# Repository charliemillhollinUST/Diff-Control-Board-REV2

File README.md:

The schematic and PCB were created in KiCad.

Contact <mill70882@stthomas.edu> for access to the software repository.

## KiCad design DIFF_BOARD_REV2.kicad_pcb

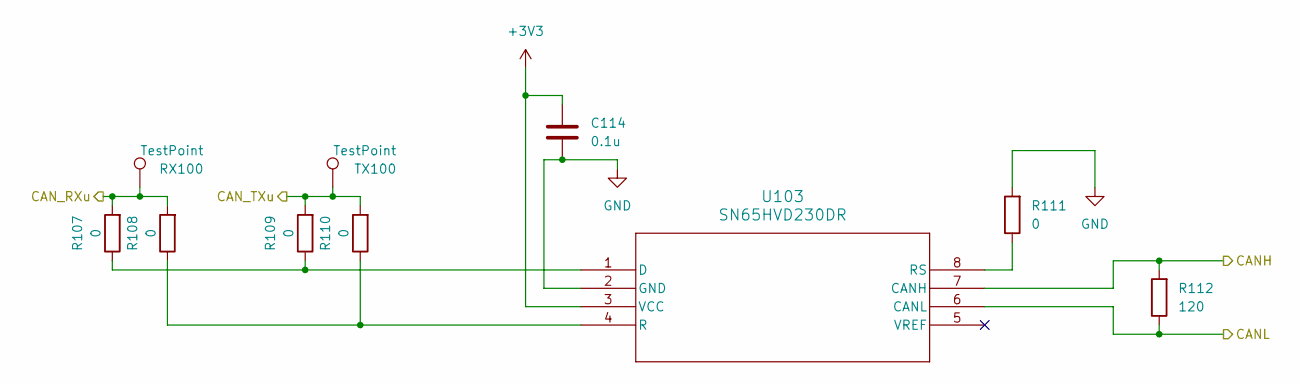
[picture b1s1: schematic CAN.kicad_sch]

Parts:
C114: 0.1u; C_0603_1608Metric_Pad1.08x0.95mm_HandSolder
R107, R108, R109, R110, R111: 0; R_0603_1608Metric_Pad0.98x0.95mm_HandSolder
R112: 120; R_0603_1608Metric_Pad0.98x0.95mm_HandSolder
RX100: TestPoint; TestPoint_Pad_D1.0mm
TX100: TestPoint; TestPoint_Pad_D1.0mm
U103: SN65HVD230DR; D8

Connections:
+3V3: C114.1, U103.3 (VCC); also elsewhere on the board
/CAN/CANH: R112.2, U103.7 (CANH); also elsewhere on the board
/CAN/CANL: R112.1, U103.6 (CANL); also elsewhere on the board
/CAN/CAN_RXu: R107.2, R108.2, RX100.1; also elsewhere on the board
/CAN/CAN_TXu: R109.2, R110.2, TX100.1; also elsewhere on the board
GND: C114.2, R111.2, U103.2 (GND); also elsewhere on the board
unnamed: R107.1, R109.1, U103.1 (D)
unnamed: R108.1, R110.1, U103.4 (R)
unnamed: R111.1, U103.8 (RS)

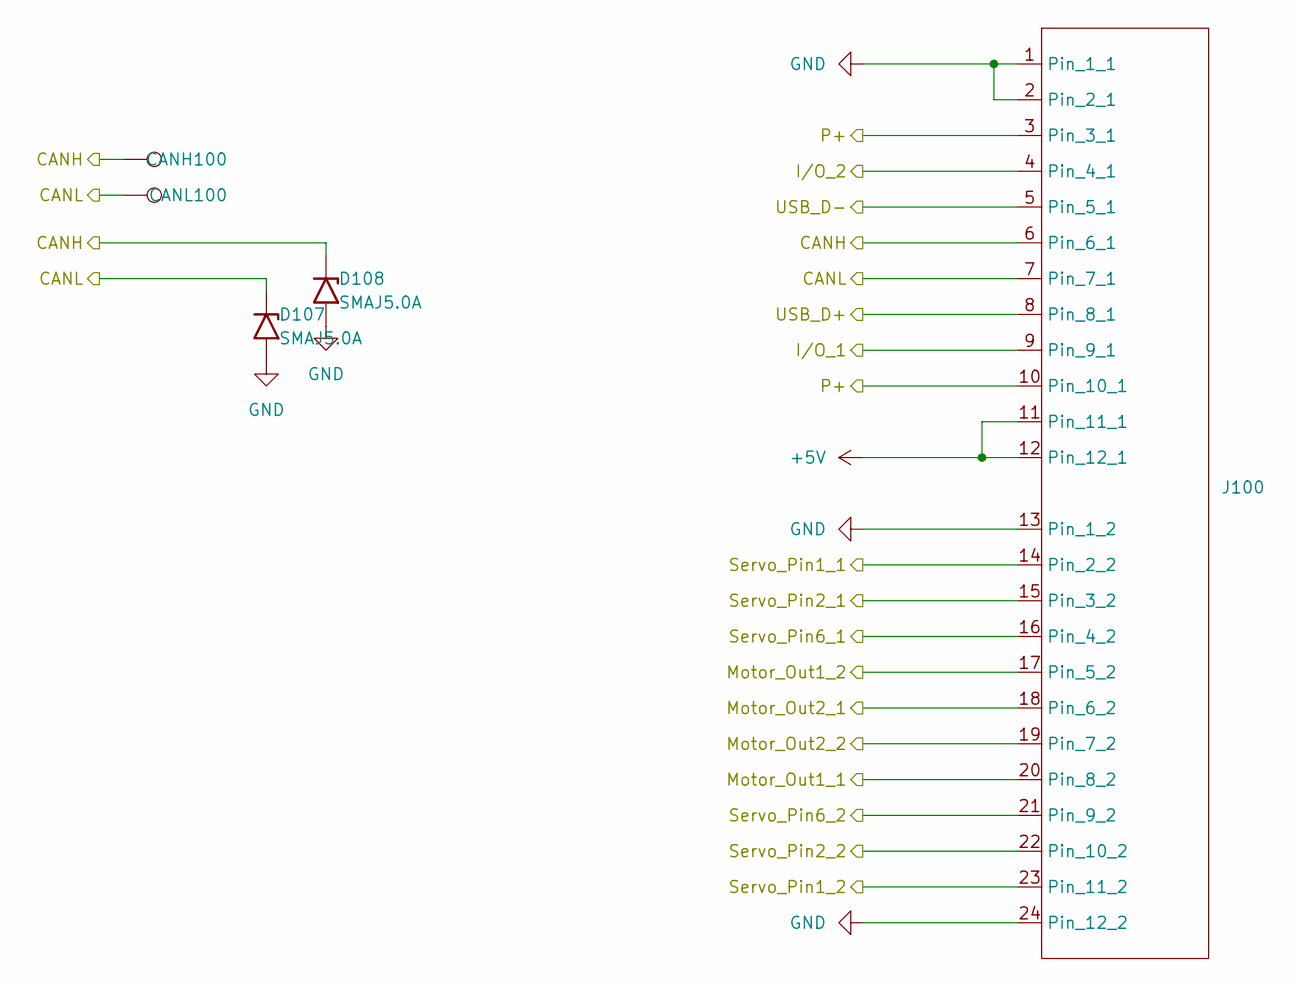
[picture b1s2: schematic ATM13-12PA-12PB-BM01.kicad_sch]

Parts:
CANH100: TestPoint; TestPoint_Pad_D1.0mm
CANL100: TestPoint; TestPoint_Pad_D1.0mm
D107, D108: SMAJ5.0A; D_SMA
J100: ATM13-12PA-12PB-BM01

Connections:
+5V: J100.11 (Pin_11_1), J100.12 (Pin_12_1); also elsewhere on the board
/Analog/Servo_Pin1_1: J100.14 (Pin_2_2); also elsewhere on the board
/Analog/Servo_Pin1_2: J100.23 (Pin_11_2); also elsewhere on the board
/Analog/Servo_Pin2_1: J100.15 (Pin_3_2); also elsewhere on the board
/Analog/Servo_Pin2_2: J100.22 (Pin_10_2); also elsewhere on the board
/Analog/Servo_Pin6_1: J100.16 (Pin_4_2); also elsewhere on the board
/Analog/Servo_Pin6_2: J100.21 (Pin_9_2); also elsewhere on the board
/CAN/CANH: CANH100.1, D108.1 (A1), J100.6 (Pin_6_1); also elsewhere on the board
/CAN/CANL: CANL100.1, D107.1 (A1), J100.7 (Pin_7_1); also elsewhere on the board
/Differential_Control/Motor_Out1_1: J100.20 (Pin_8_2); also elsewhere on the board
/Differential_Control/Motor_Out1_2: J100.19 (Pin_7_2); also elsewhere on the board
/Differential_Control/Motor_Out2_1: J100.17 (Pin_5_2); also elsewhere on the board
/Differential_Control/Motor_Out2_2: J100.18 (Pin_6_2); also elsewhere on the board
/Enclosure Connectors/I/O_1: J100.9 (Pin_9_1); also elsewhere on the board
/Enclosure Connectors/I/O_2: J100.4 (Pin_4_1); also elsewhere on the board
/Enclosure Connectors/P+: J100.3 (Pin_3_1), J100.10 (Pin_10_1); also elsewhere on the board
/Enclosure Connectors/USB_D+: J100.8 (Pin_8_1); also elsewhere on the board
/Enclosure Connectors/USB_D-: J100.5 (Pin_5_1); also elsewhere on the board
GND: D107.2 (A2), D108.2 (A2), J100.1 (Pin_1_1), J100.2 (Pin_2_1), J100.13 (Pin_1_2), J100.24 (Pin_12_2); also elsewhere on the board

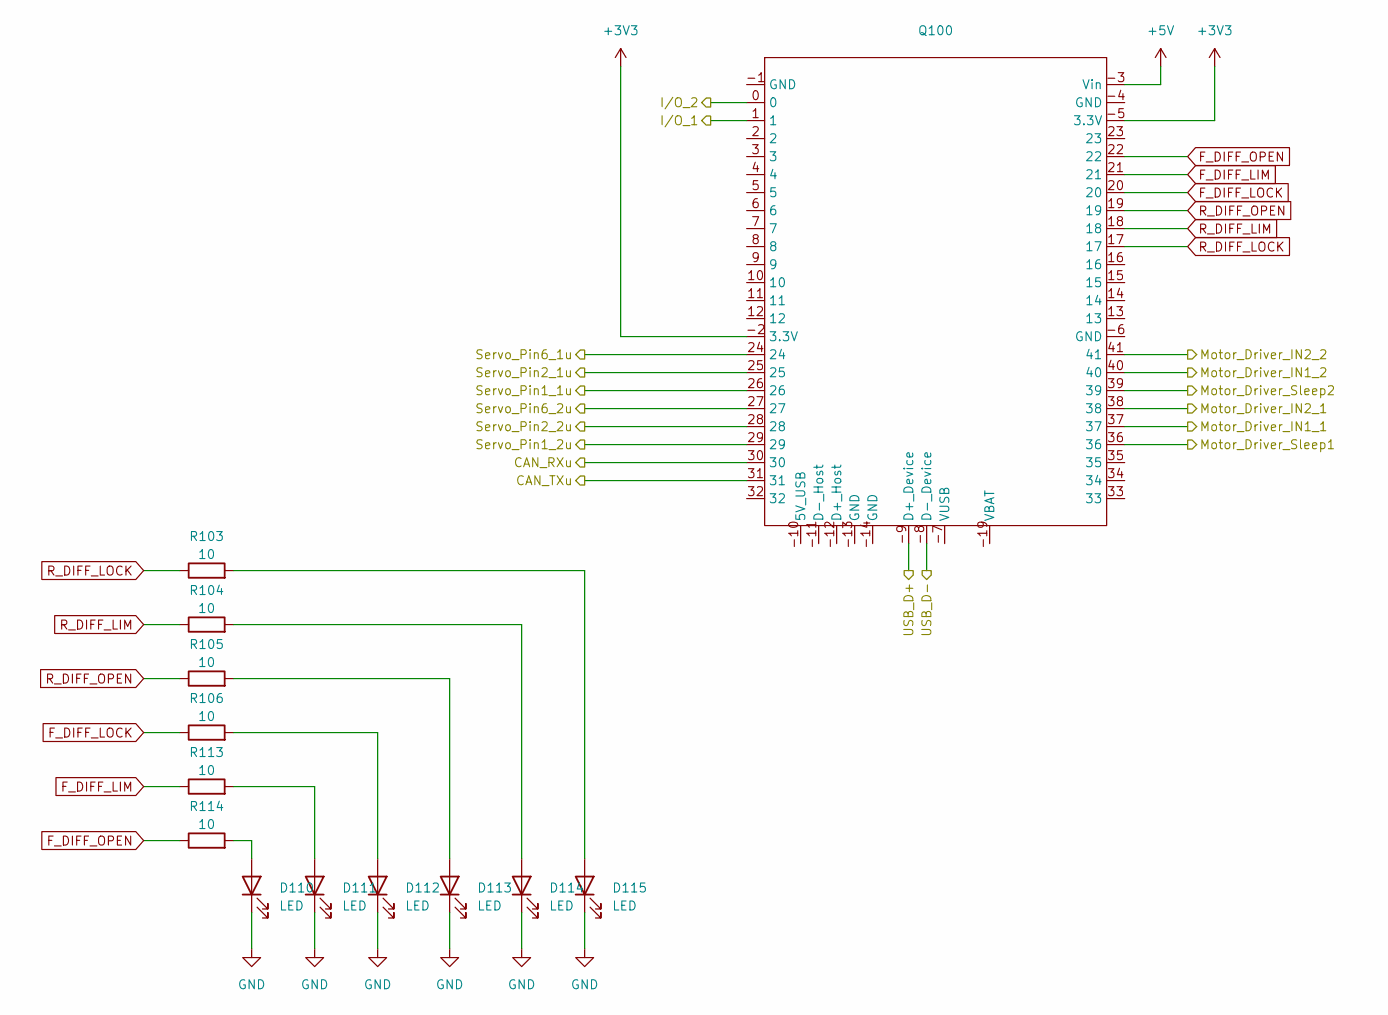
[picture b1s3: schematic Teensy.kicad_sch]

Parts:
D110, D111, D112, D113, D114, D115: LED; LED_0603_1608Metric_Pad1.05x0.95mm_HandSolder
Q100: Teensy4_1
R103, R104, R105, R106, R113, R114: 10; R_0603_1608Metric_Pad0.98x0.95mm_HandSolder

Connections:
+3V3: Q100.-2 (3.3V), Q100.-5 (3.3V); also elsewhere on the board
+5V: Q100.-3 (Vin); also elsewhere on the board
/Analog/Servo_Pin1_1: Q100.26; also elsewhere on the board
/Analog/Servo_Pin1_2: Q100.29; also elsewhere on the board
/Analog/Servo_Pin2_1: Q100.25; also elsewhere on the board
/Analog/Servo_Pin2_2: Q100.28; also elsewhere on the board
/Analog/Servo_Pin6_1: Q100.24; also elsewhere on the board
/Analog/Servo_Pin6_2: Q100.27; also elsewhere on the board
/CAN/CAN_RXu: Q100.30; also elsewhere on the board
/CAN/CAN_TXu: Q100.31; also elsewhere on the board
/Differential_Control/Motor_Driver_IN1_1: Q100.37; also elsewhere on the board
/Differential_Control/Motor_Driver_IN1_2: Q100.40; also elsewhere on the board
/Differential_Control/Motor_Driver_IN2_1: Q100.38; also elsewhere on the board
/Differential_Control/Motor_Driver_IN2_2: Q100.41; also elsewhere on the board
/Differential_Control/Motor_Driver_Sleep1: Q100.36; also elsewhere on the board
/Differential_Control/Motor_Driver_Sleep2: Q100.39; also elsewhere on the board
/Enclosure Connectors/I/O_1: Q100.1; also elsewhere on the board
/Enclosure Connectors/I/O_2: Q100.0; also elsewhere on the board
/Enclosure Connectors/USB_D+: Q100.-9 (D+_Device); also elsewhere on the board
/Enclosure Connectors/USB_D-: Q100.-8 (D-_Device); also elsewhere on the board
F_DIFF_LIM: Q100.21, R113.1
F_DIFF_LOCK: Q100.20, R106.1
F_DIFF_OPEN: Q100.22, R114.1
GND: D110.1 (K), D111.1 (K), D112.1 (K), D113.1 (K), D114.1 (K), D115.1 (K); also elsewhere on the board
unnamed: D110.2 (A), R114.2
unnamed: D111.2 (A), R113.2
unnamed: D112.2 (A), R106.2
unnamed: D113.2 (A), R105.2
unnamed: D114.2 (A), R104.2
unnamed: D115.2 (A), R103.2
R_DIFF_LIM: Q100.18, R104.1
R_DIFF_LOCK: Q100.17, R103.1
R_DIFF_OPEN: Q100.19, R105.1

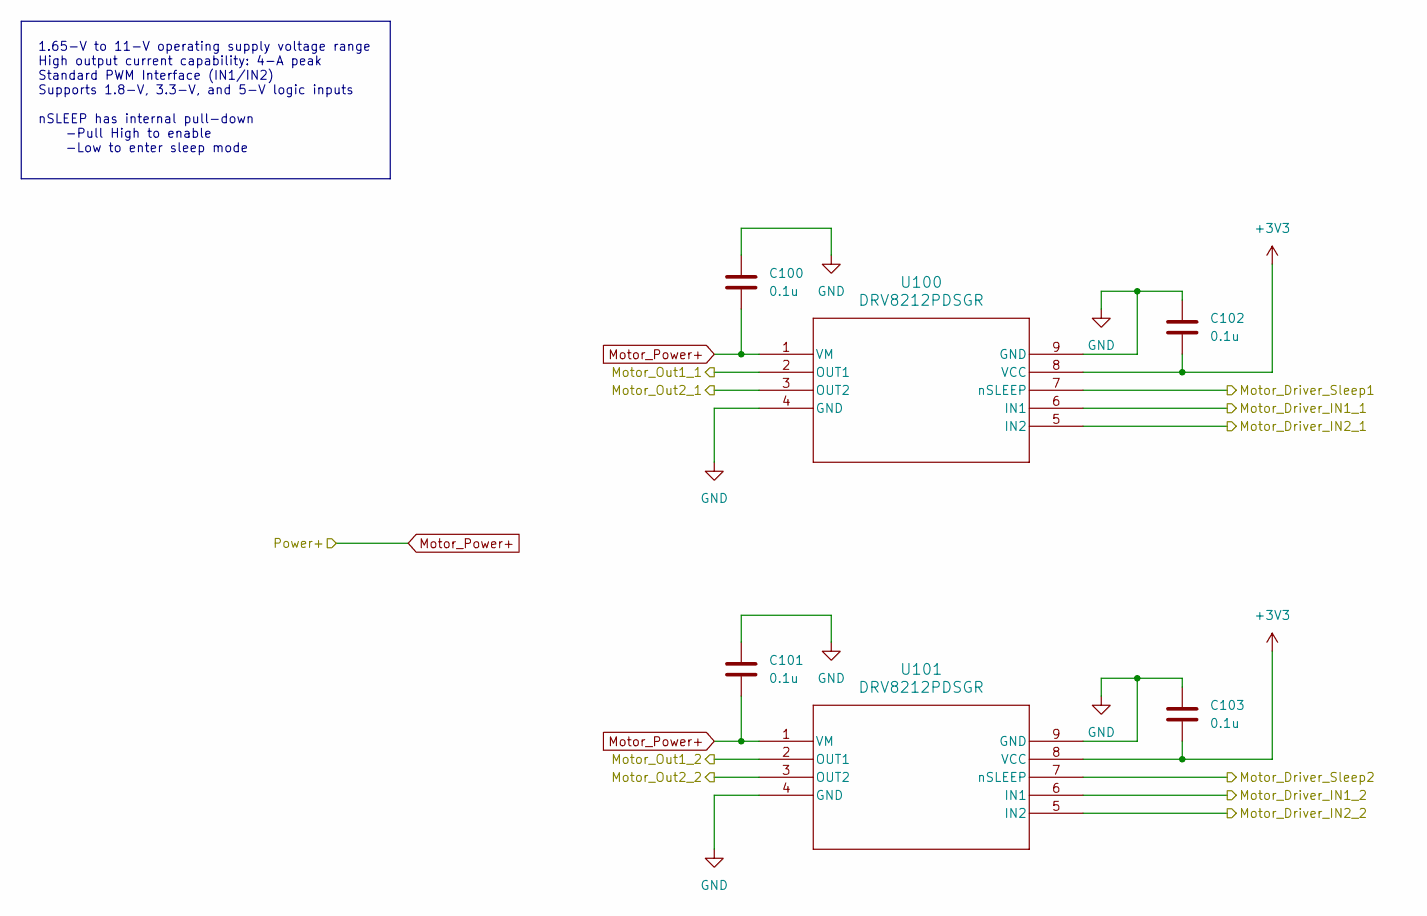
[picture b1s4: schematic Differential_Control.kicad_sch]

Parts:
C100, C101, C102, C103: 0.1u; C_0603_1608Metric_Pad1.08x0.95mm_HandSolder
U100, U101: DRV8212PDSGR; WSON8_DSG_TEX

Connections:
+3V3: C102.2, C103.2, U100.8 (VCC), U101.8 (VCC); also elsewhere on the board
/Differential_Control/Motor_Driver_IN1_1: U100.6 (IN1); also elsewhere on the board
/Differential_Control/Motor_Driver_IN1_2: U101.6 (IN1); also elsewhere on the board
/Differential_Control/Motor_Driver_IN2_1: U100.5 (IN2); also elsewhere on the board
/Differential_Control/Motor_Driver_IN2_2: U101.5 (IN2); also elsewhere on the board
/Differential_Control/Motor_Driver_Sleep1: U100.7 (nSLEEP); also elsewhere on the board
/Differential_Control/Motor_Driver_Sleep2: U101.7 (nSLEEP); also elsewhere on the board
/Differential_Control/Motor_Out1_1: U100.2 (OUT1); also elsewhere on the board
/Differential_Control/Motor_Out1_2: U101.2 (OUT1); also elsewhere on the board
/Differential_Control/Motor_Out2_1: U100.3 (OUT2); also elsewhere on the board
/Differential_Control/Motor_Out2_2: U101.3 (OUT2); also elsewhere on the board
GND: C100.1, C101.1, C102.1, C103.1, U100.4 (GND), U100.9 (GND), U101.4 (GND), U101.9 (GND); also elsewhere on the board
Motor_Power+: C100.2, C101.2, U100.1 (VM), U101.1 (VM); also elsewhere on the board

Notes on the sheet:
1.65-V to 11-V operating supply voltage range High output current capability: 4-A peak Standard PWM Interface (IN1/IN2) Supports 1.8-V, 3.3-V, and 5-V logic inputs nSLEEP has internal pull-down -Pull High to enable -Low to enter sleep mode

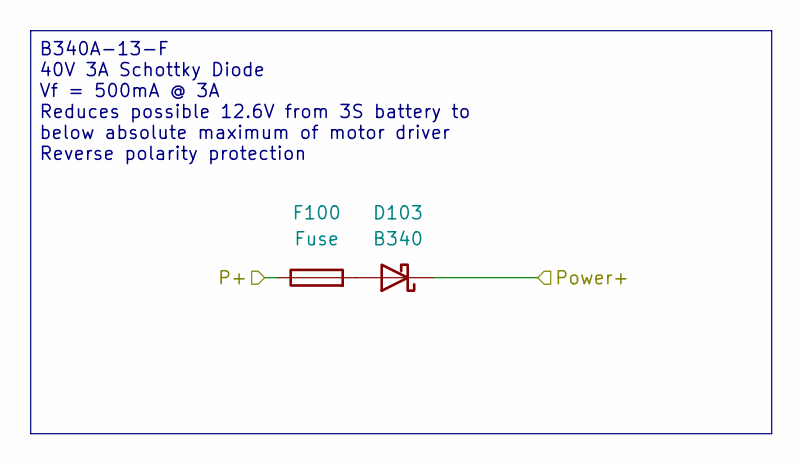
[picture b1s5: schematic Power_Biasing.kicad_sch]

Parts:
D103: B340; D_SMC
F100: Fuse; Fuse_1206_3216Metric

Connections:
/Enclosure Connectors/P+: F100.1; also elsewhere on the board
Motor_Power+: D103.1 (K); also elsewhere on the board
unnamed: D103.2 (A), F100.2

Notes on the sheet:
B340A-13-F 40V 3A Schottky Diode Vf = 500mA @ 3A Reduces possible 12.6V from 3S battery to below absolute maximum of motor driver Reverse polarity protection

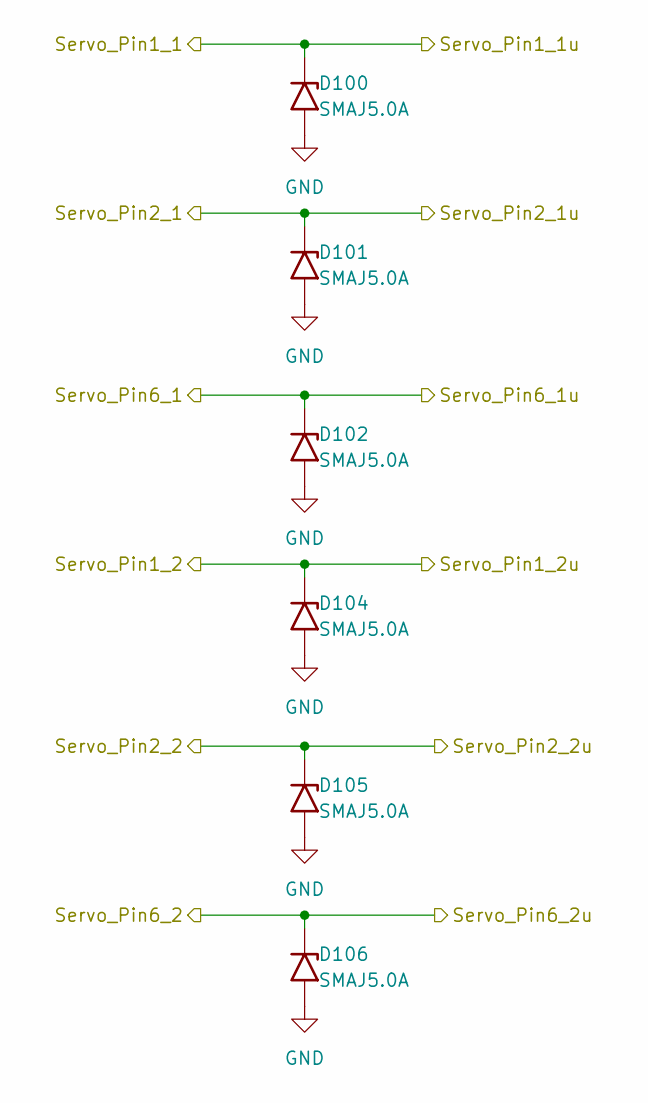
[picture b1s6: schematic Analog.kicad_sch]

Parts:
D100, D101, D102, D104, D105, D106: SMAJ5.0A; D_SMA

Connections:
/Analog/Servo_Pin1_1: D100.1 (A1); also elsewhere on the board
/Analog/Servo_Pin1_2: D104.1 (A1); also elsewhere on the board
/Analog/Servo_Pin2_1: D101.1 (A1); also elsewhere on the board
/Analog/Servo_Pin2_2: D105.1 (A1); also elsewhere on the board
/Analog/Servo_Pin6_1: D102.1 (A1); also elsewhere on the board
/Analog/Servo_Pin6_2: D106.1 (A1); also elsewhere on the board
GND: D100.2 (A2), D101.2 (A2), D102.2 (A2), D104.2 (A2), D105.2 (A2), D106.2 (A2); also elsewhere on the board

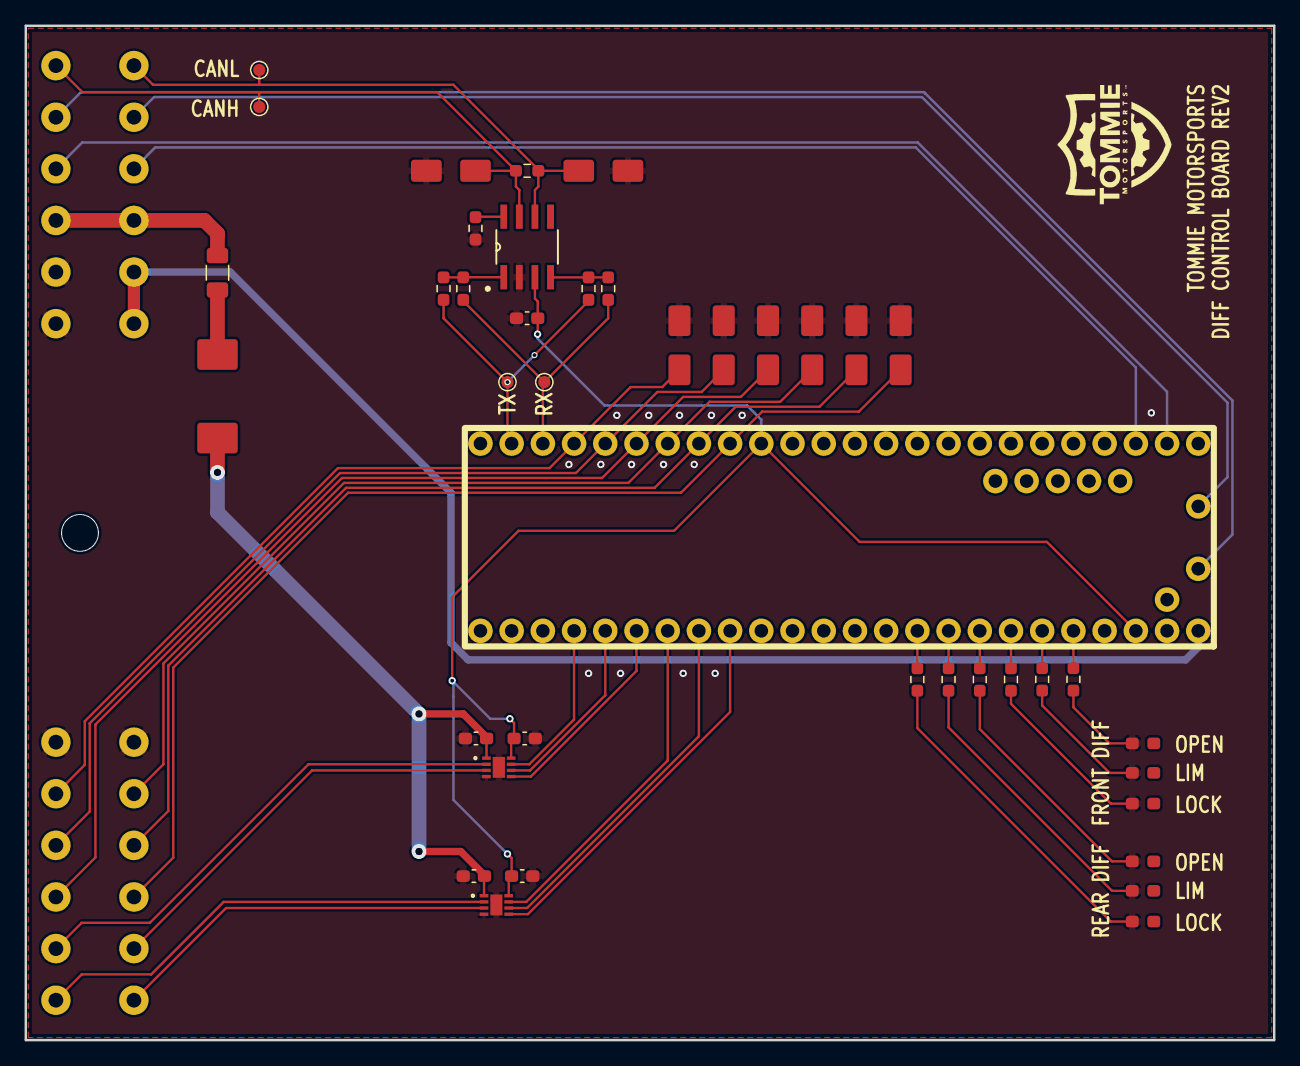
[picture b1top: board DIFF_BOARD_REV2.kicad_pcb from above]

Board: 2 copper layers, 101.6 x 82.6 mm, 42 parts (0 on the bottom side), 45 nets.

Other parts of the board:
CANH: TestPoint; TestPoint_Pad_D1.0mm
CANL: TestPoint; TestPoint_Pad_D1.0mm
RX: TestPoint; TestPoint_Pad_D1.0mm
TX: TestPoint; TestPoint_Pad_D1.0mm

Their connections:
/CAN/CANH: CANH.1; also elsewhere on the board
/CAN/CANL: CANL.1; also elsewhere on the board
/CAN/CAN_RXu: RX.1; also elsewhere on the board
/CAN/CAN_TXu: TX.1; also elsewhere on the board

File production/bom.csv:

Designator,Footprint,Quantity,Value,LCSC Part #
"C100, C101, C102, C103, C114",0603,5,0.1u,
"CANH, CANL, RX, TX",TestPoint_Pad_D1.0mm,4,TestPoint,
"D100, D101, D102, D104, D105, D106, D107, D108",D_SMA,8,SMAJ5.0A,
D103,D_SMC,1,B340,
"D110, D111, D112, D113, D114, D115",0603,6,LED,
F100,1206,1,Fuse,
J100,ATM13-12PA-12PB-BM01,1,~,
Q100,Teensy4_1,1,~,
"R103, R104, R105, R106, R113, R114",0603,6,10,
"R107, R108, R109, R110, R111",0603,5,0,
R112,0603,1,120,
"U100, U101",WSON8_DSG_TEX,2,DRV8212PDSGR,
U103,D8,1,SN65HVD230DR,

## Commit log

2025-02-12 initial release
2025-02-12 re-ran fabrication toolkit and iBOM generation
2025-02-12 updated QR code on silkscreen to match github repository
2025-02-12 added images
2025-02-12 added fuse and made power nets thicker
2025-02-12 updated silkscreen
2025-02-14 commit for sanity
2025-02-14 larger silkscreen
2025-02-15 Updated silkscreen. Re-ran fab toolkit and iBOM. Looking to order soon
2025-02-15 added new images
